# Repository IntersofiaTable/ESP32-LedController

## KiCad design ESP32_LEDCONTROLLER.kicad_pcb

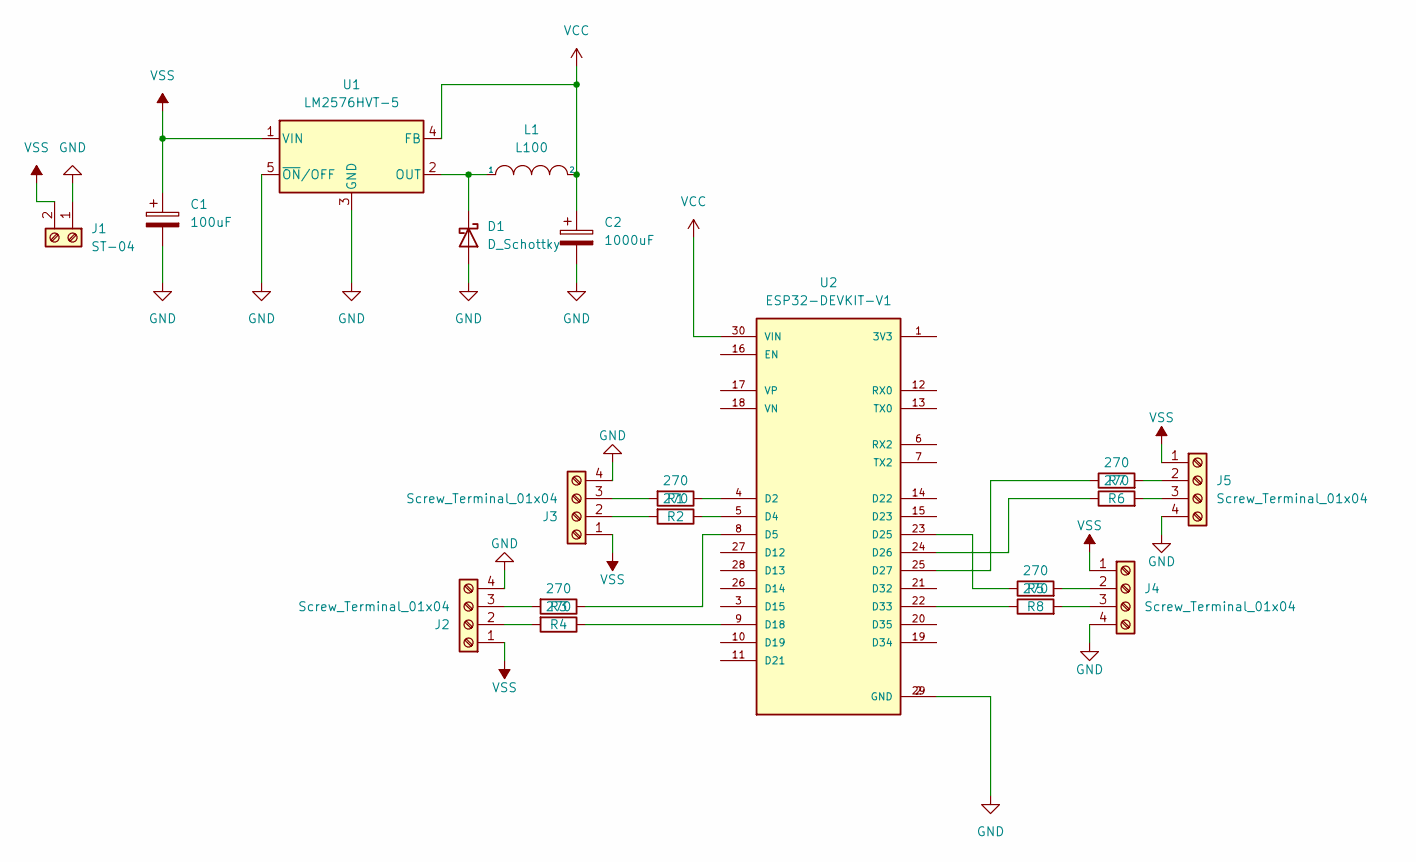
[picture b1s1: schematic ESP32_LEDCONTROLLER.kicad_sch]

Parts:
C1: 100uF; CP_Radial_D8.0mm_P3.50mm
C2: 1000uF; CP_Radial_D10.0mm_P5.00mm
D1: D_Schottky; D_DO-27_P12.70mm_Horizontal
J1: ST-04; TerminalBlock_bornier-2_P5.08mm
J2, J3, J4, J5: Screw_Terminal_01x04; TerminalBlock_4Ucon_1x04_P3.50mm_Horizontal
L1: L100; L_Radial_D9.5mm_P5.00mm_Fastron_07HVP
R1, R2, R3, R4, R5, R6, R7, R8: 270; R_Axial_DIN0207_L6.3mm_D2.5mm_P7.62mm_Horizontal
U1: LM2576HVT-5; TO-220-5_Vertical
U2: ESP32-DEVKIT-V1; MODULE_ESP32_DEVKIT_V1; PARTREV N/A

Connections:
GND: C1.2, C2.2, D1.2 (A), J1.1, J2.4, J3.4, J4.4, J5.4, U1.3 (GND), U1.5 (~ON/OFF), U2.2 (GND), U2.29 (GND)
unnamed: D1.1 (K), L1.1, U1.2 (OUT)
unnamed: J2.2, R4.2
unnamed: J2.3, R3.2
unnamed: J3.2, R2.2
unnamed: J3.3, R1.2
unnamed: J4.2, R5.2
unnamed: J4.3, R8.2
unnamed: J5.2, R7.2
unnamed: J5.3, R6.2
unnamed: R1.1, U2.4 (D2)
unnamed: R2.1, U2.5 (D4)
unnamed: R3.1, U2.8 (D5)
unnamed: R4.1, U2.9 (D18)
unnamed: R5.1, U2.23 (D25)
unnamed: R6.1, U2.24 (D26)
unnamed: R7.1, U2.25 (D27)
unnamed: R8.1, U2.22 (D33)
VCC: C2.1, L1.2, U1.4 (FB), U2.30 (VIN)
VSS: C1.1, J1.2, J2.1, J3.1, J4.1, J5.1, U1.1 (VIN)

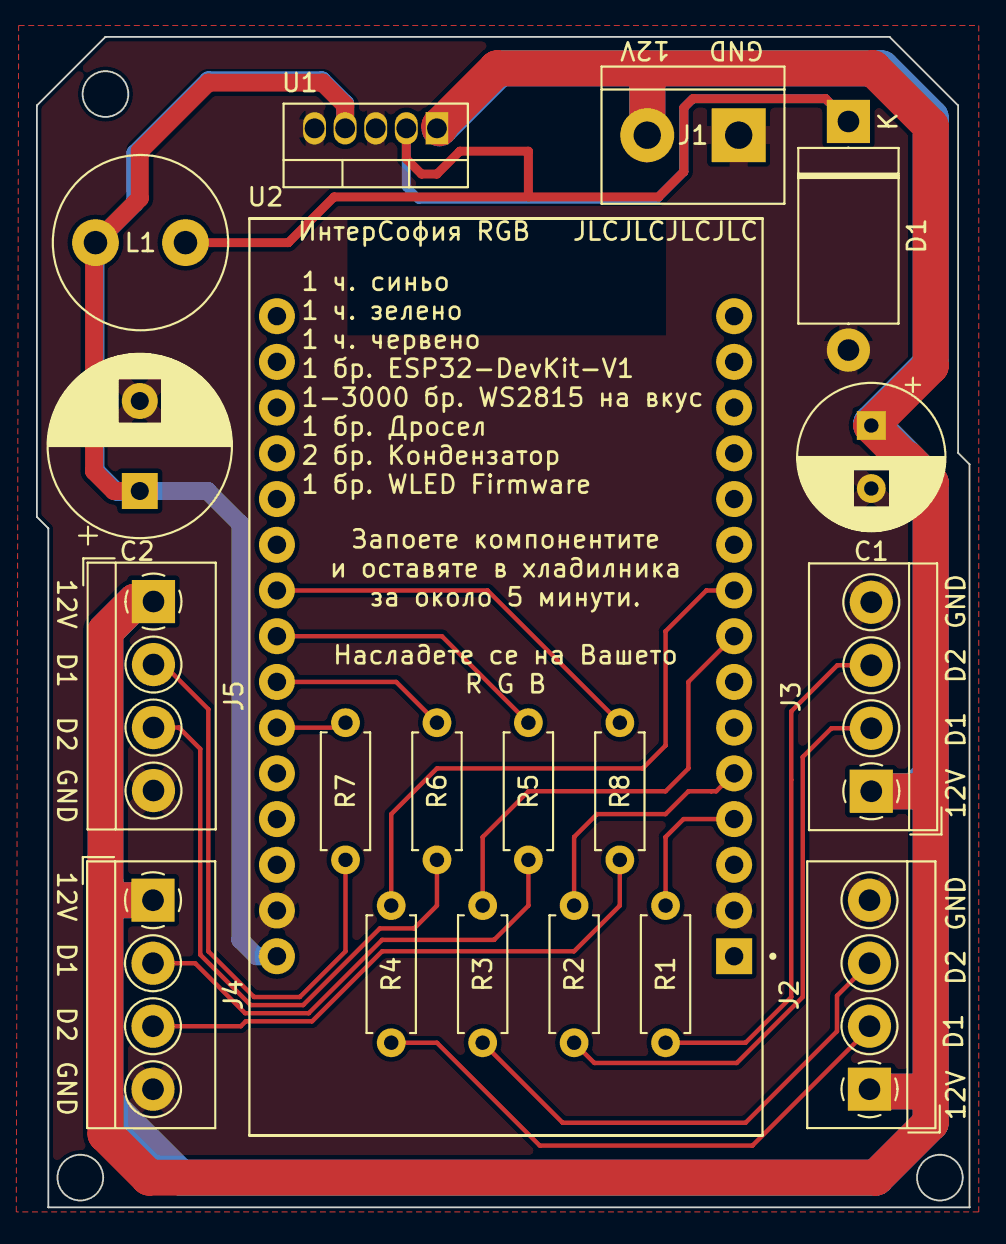
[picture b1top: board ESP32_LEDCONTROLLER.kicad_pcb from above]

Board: 2 copper layers, 51.8 x 65.0 mm, 19 parts (0 on the bottom side), 20 nets.

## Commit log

2022-12-12 ESP32 LED Controller initial Commit
2022-12-12 add gitignore
2022-12-23 v0.1 of the LED Controller has been completed.
2022-12-23 upload table
2022-12-31 update gitignore to remove backups
2023-01-01 Refactor by dropping level shifter & changing board layout
2023-01-01 update & add gerbers
2023-01-02 graphics & shitposting
